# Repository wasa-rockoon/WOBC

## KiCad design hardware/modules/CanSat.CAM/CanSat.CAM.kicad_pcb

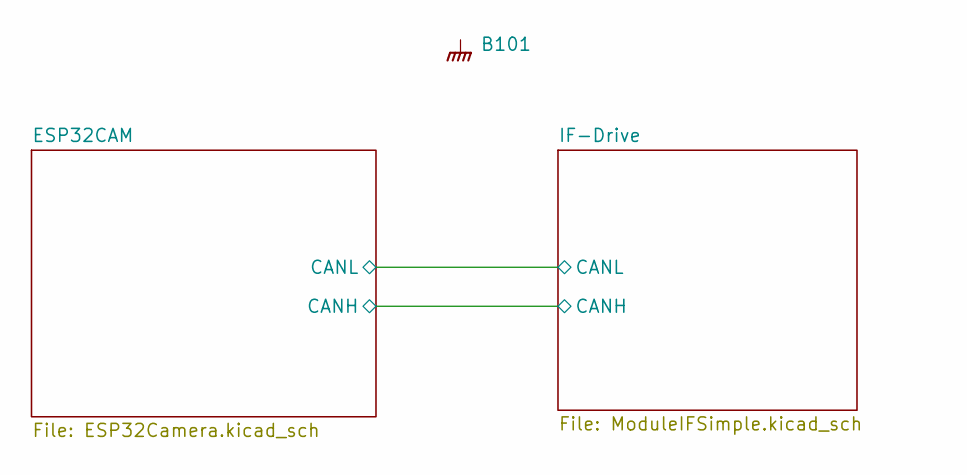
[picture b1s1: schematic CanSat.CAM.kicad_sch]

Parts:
B101: Board_0.5U_60x40

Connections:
GND: B101.GND; also elsewhere on the board

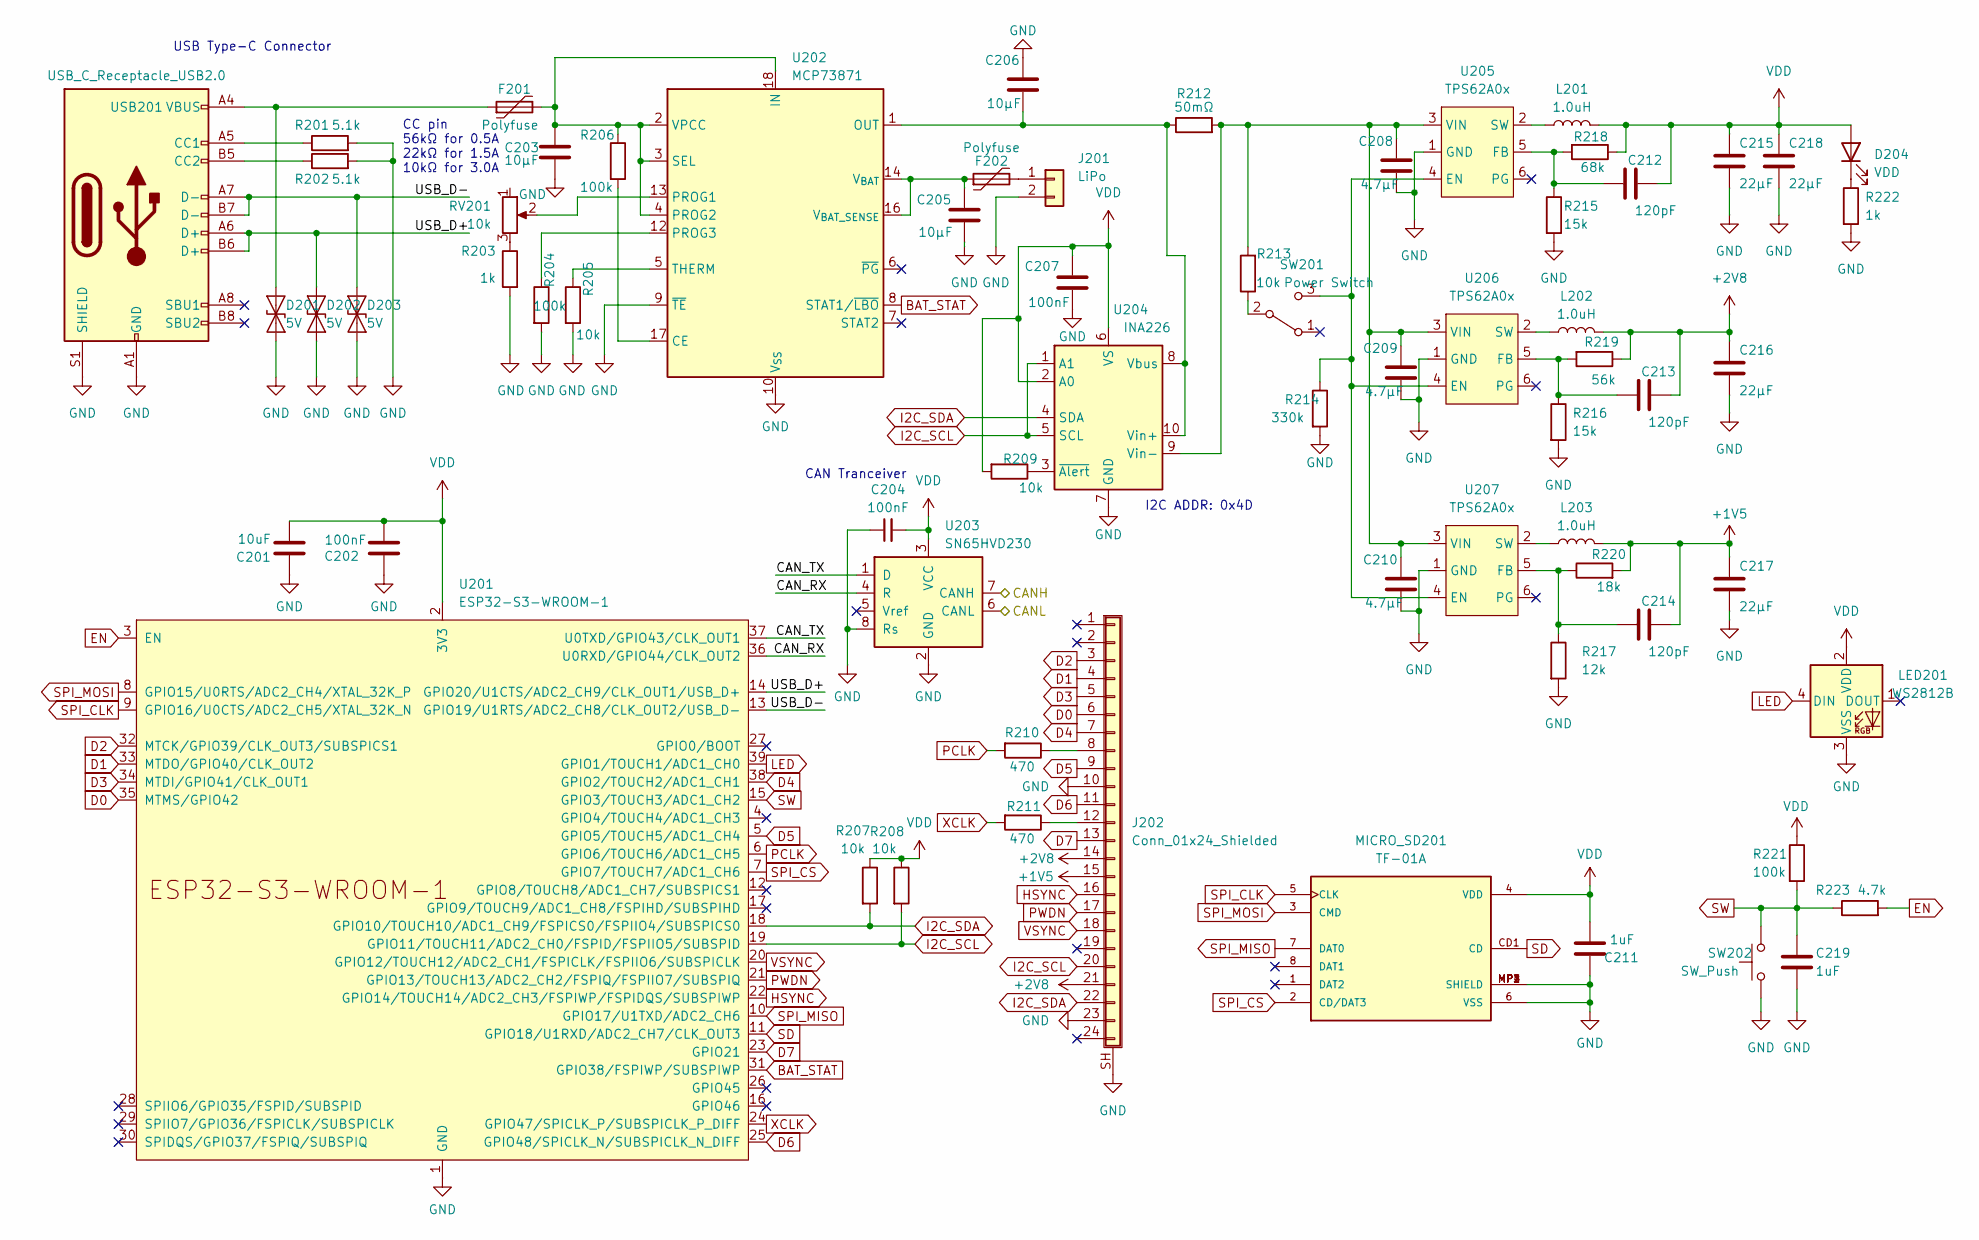
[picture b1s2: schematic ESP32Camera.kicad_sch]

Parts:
C201: 10uF; C_0603_1608Metric; LCSC C96446
C202, C204, C207: 100nF; C_0402_1005Metric; LCSC C1525
C203, C205, C206: 10µF; C_0603_1608Metric; LCSC C96446
C208, C209, C210: 4.7µF; C_0603_1608Metric; LCSC C19666
C211, C219: 1uF; C_0402_1005Metric; LCSC C52923
C212, C213, C214: 120pF; C_0402_1005Metric_Pad0.74x0.62mm_HandSolder; LCSC C307442
C215, C216, C217, C218: 22µF; C_0805_2012Metric; LCSC C45783
D201, D202, D203: 5V; D_SOD-882; LCSC C7420372
D204: VDD; LED_0805_2012Metric; LCSC C2297
F201, F202: Polyfuse; Fuse_1206_3216Metric; LCSC C883133
J201: LiPo; JST_PH_S2B-PH-K_1x02_P2.00mm_Horizontal
J202: Conn_01x24_Shielded; FPC-SMD_24P-P0.50_HCTL_HC-FPC-05-10-24RLTAG
L201, L202, L203: 1.0uH; L_Murata_DFE201610P; LCSC C882953
LED201: WS2812B; LED_XL-1615RGBC-WS2812B; LCSC C5349954
MICRO_SD201: TF-01A; LCSC C5155563
R201, R202: 5.1k; R_0402_1005Metric; LCSC C25905
R203, R222: 1k; R_0402_1005Metric; LCSC C11702
R204, R206, R221: 100k; R_0402_1005Metric; LCSC C25741
R205, R207, R208, R209, R213: 10k; R_0402_1005Metric; LCSC C25744
R210, R211: 470; R_0402_1005Metric; LCSC C25117
R212: 50mΩ; R_0805_2012Metric; LCSC C247602
R214: 330k; R_0402_1005Metric; LCSC C25778
R215, R216: 15k; R_0402_1005Metric; LCSC C25756
R217: 12k; R_0402_1005Metric; LCSC C25752
R218: 68k; R_0402_1005Metric; LCSC C36871
R219: 56k; R_0402_1005Metric; LCSC C25796
R220: 18k; R_0402_1005Metric; LCSC C25762
R223: 4.7k; R_0402_1005Metric; LCSC C25900
RV201: 10k; Potentiometer_Bourns_TC33X_Vertical; LCSC C719176
SW201: Power Switch; SW_Slide_SPDT_Straight_CK_OS102011MS2Q
SW202: SW_Push; TVAF06-A020B-R
U201: ESP32-S3-WROOM-1
U202: MCP73871; QFN-20-1EP_4x4mm_P0.5mm_EP2.5x2.5mm; LCSC C511310
U203: SN65HVD230; SOIC-8_3.9x4.9mm_P1.27mm; LCSC C12084
U204: INA226; VSSOP-10_3x3mm_P0.5mm; LCSC C49851
U205, U206, U207: TPS62A0x; SOT-563; LCSC C5350187
USB201: USB_C_Receptacle_USB2.0; USB_C_TYPEC-301S-ACP16X7; LCSC C2856766

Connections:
+1V5: C214.1, C217.1, J202.15, L203.2, R220.2
+2V8: C213.1, C216.1, J202.14, J202.21, L202.2, R219.1
/ESP32CAM/CANH: U203.7 (CANH); also elsewhere on the board
/ESP32CAM/CANL: U203.6 (CANL); also elsewhere on the board
/ESP32CAM/CAN_RX: U201.36 (U0RXD/GPIO44/CLK_OUT2), U203.4 (R)
/ESP32CAM/CAN_TX: U201.37 (U0TXD/GPIO43/CLK_OUT1), U203.1 (D)
/ESP32CAM/USB_D+: D202.2 (A2), U201.14 (GPIO20/U1CTS/ADC2_CH9/CLK_OUT1/USB_D+), USB201.A6 (D+), USB201.B6 (D+)
/ESP32CAM/USB_D-: D203.2 (A2), U201.13 (GPIO19/U1RTS/ADC2_CH8/CLK_OUT2/USB_D-), USB201.A7 (D-), USB201.B7 (D-)
BAT_STAT: U201.31 (GPIO38/FSPIWP/SUBSPIWP), U202.8 (STAT1/~LBO)
D0: J202.6, U201.35 (MTMS/GPIO42)
D1: J202.4, U201.33 (MTDO/GPIO40/CLK_OUT2)
D2: J202.3, U201.32 (MTCK/GPIO39/CLK_OUT3/SUBSPICS1)
D3: J202.5, U201.34 (MTDI/GPIO41/CLK_OUT1)
D4: J202.7, U201.38 (GPIO2/TOUCH2/ADC1_CH1)
D5: J202.9, U201.5 (GPIO5/TOUCH5/ADC1_CH4)
D6: J202.11, U201.25 (GPIO48/SPICLK_N/SUBSPICLK_N_DIFF)
D7: J202.13, U201.23 (GPIO21)
EN: R223.2, U201.3 (EN)
GND: C201.1, C202.1, C203.2, C204.1, C205.2, C206.1, C207.2, C208.2, C209.2, C210.2, C211.1, C215.2, C216.2, C217.2, C218.2, C219.2, D201.1 (A1), D202.1 (A1), D203.1 (A1), J201.2, J202.10, J202.23, J202.SH (Shield), LED201.3 (VSS), MICRO_SD201.6 (VSS), MICRO_SD201.MP1 (SHIELD), MICRO_SD201.MP2 (SHIELD), MICRO_SD201.MP3 (SHIELD), MICRO_SD201.MP4 (SHIELD), R201.2, R202.2, R203.2, R204.2, R205.2, R214.2, R215.2, R216.2, R217.2, R222.2, SW202.1, U201.1 (GND), U201.40 (GND), U201.41 (GND), U202.9 (~TE), U202.10 (V_{SS}), U202.11 (V_{SS}), U202.21 (V_{SS}), U203.2 (GND), U203.8 (Rs), U204.7 (GND), U205.1 (GND), U206.1 (GND), U207.1 (GND), USB201.A1 (GND), USB201.A12 (GND), USB201.B1 (GND), USB201.B12 (GND), USB201.S1 (SHIELD); also elsewhere on the board
HSYNC: J202.16, U201.22 (GPIO14/TOUCH14/ADC2_CH3/FSPIWP/FSPIDQS/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)
I2C_SCL: J202.20, R208.2, U201.19 (GPIO11/TOUCH11/ADC2_CH0/FSPID/FSPIIO5/S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), U204.1 (A1), U204.5 (SCL)
I2C_SDA: J202.22, R207.2, U201.18 (GPIO10/TOUCH10/ADC1_CH9/FSPICS0/FSPIIO4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), U204.4 (SDA)
LED: LED201.4 (DIN), U201.39 (GPIO1/TOUCH1/ADC1_CH0)
unnamed: D201.2 (A2), F201.1, USB201.A4 (VBUS), USB201.A9 (VBUS), USB201.B4 (VBUS), USB201.B9 (VBUS)
unnamed: D204.1 (K), R222.1
unnamed: F202.2, J201.1
unnamed: J202.8, R210.1
unnamed: J202.12, R211.1
unnamed: R203.1, RV201.3
unnamed: R213.1, SW201.2 (B)
unnamed: R214.1, SW201.3 (C), U205.4 (EN), U206.4 (EN), U207.4 (EN)
unnamed: R206.2, U202.17 (CE)
unnamed: RV201.2, U202.13 (PROG1)
unnamed: C203.1, F201.2, R206.1, U202.2 (VPCC), U202.3 (SEL), U202.4 (PROG2), U202.18 (IN), U202.19 (IN)
unnamed: R204.1, U202.12 (PROG3)
unnamed: R205.1, U202.5 (THERM)
unnamed: C205.1, F202.1, U202.14 (V_{BAT}), U202.15 (V_{BAT}), U202.16 (V_{BAT_SENSE})
unnamed: C206.2, R212.1, U202.1 (OUT), U202.20 (OUT), U204.8 (Vbus), U204.10 (Vin+)
unnamed: C208.1, C209.1, C210.1, R212.2, R213.2, U204.9 (Vin-), U205.3 (VIN), U206.3 (VIN), U207.3 (VIN)
unnamed: R209.1, U204.3 (~Alert)
unnamed: C212.2, R215.1, R218.2, U205.5 (FB)
unnamed: L201.1, U205.2 (SW)
unnamed: C213.2, R216.1, R219.2, U206.5 (FB)
unnamed: L202.1, U206.2 (SW)
unnamed: C214.2, R217.1, R220.1, U207.5 (FB)
unnamed: L203.1, U207.2 (SW)
unnamed: R201.1, USB201.A5 (CC1)
unnamed: R202.1, USB201.B5 (CC2)
PCLK: R210.2, U201.6 (GPIO6/TOUCH6/ADC1_CH5)
PWDN: J202.17, U201.21 (GPIO13/TOUCH13/ADC2_CH2/FSPIQ/FSPIIO7/S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)
SD: MICRO_SD201.CD1 (CD), U201.11 (GPIO18/U1RXD/ADC2_CH7/CLK_OUT3)
SPI_CLK: MICRO_SD201.5 (CLK), U201.9 (GPIO16/U0CTS/ADC2_CH5/XTAL_32K_N)
SPI_CS: MICRO_SD201.2 (CD/DAT3), U201.7 (GPIO7/TOUCH7/ADC1_CH6)
SPI_MISO: MICRO_SD201.7 (DAT0), U201.10 (GPIO17/U1TXD/ADC2_CH6)
SPI_MOSI: MICRO_SD201.3 (CMD), U201.8 (GPIO15/U0RTS/ADC2_CH4/XTAL_32K_P)
SW: C219.1, R221.2, R223.1, SW202.2, U201.15 (GPIO3/TOUCH3/ADC1_CH2)
VDD: C201.2, C202.2, C204.2, C207.1, C211.2, C212.1, C215.1, C218.1, D204.2 (A), L201.2, LED201.2 (VDD), MICRO_SD201.4 (VDD), R207.1, R208.1, R209.2, R218.1, R221.1, U201.2 (3V3), U203.3 (VCC), U204.2 (A0), U204.6 (VS)
VSYNC: J202.18, U201.20 (GPIO12/TOUCH12/ADC2_CH1/FSPICLK/FSPIIO6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)
XCLK: R211.2, U201.24 (GPIO47/SPICLK_P/SUBSPICLK_P_DIFF)

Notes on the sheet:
USB Type-C Connector
CAN Tranceiver
CC pin 56kΩ for 0.5A 22kΩ for 1.5A 10kΩ for 3.0A
I2C ADDR: 0x4D

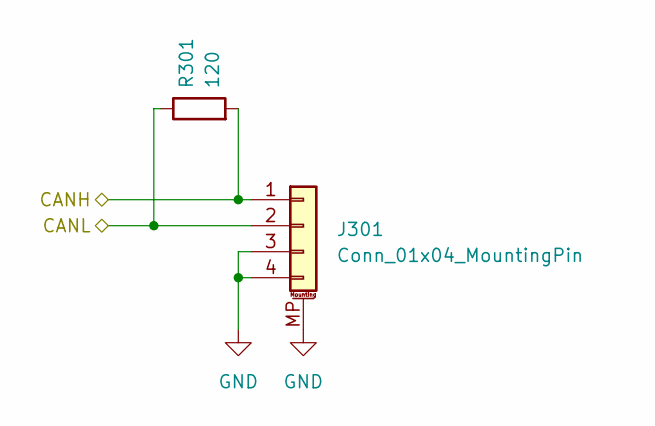
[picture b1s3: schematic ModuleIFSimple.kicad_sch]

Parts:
J301: Conn_01x04_MountingPin; Grove_4P_L_SMD
R301: 120; R_0402_1005Metric; LCSC C25079

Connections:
/ESP32CAM/CANH: J301.1, R301.2; also elsewhere on the board
/ESP32CAM/CANL: J301.2, R301.1; also elsewhere on the board
GND: J301.3, J301.4, J301.MP (MountPin); also elsewhere on the board

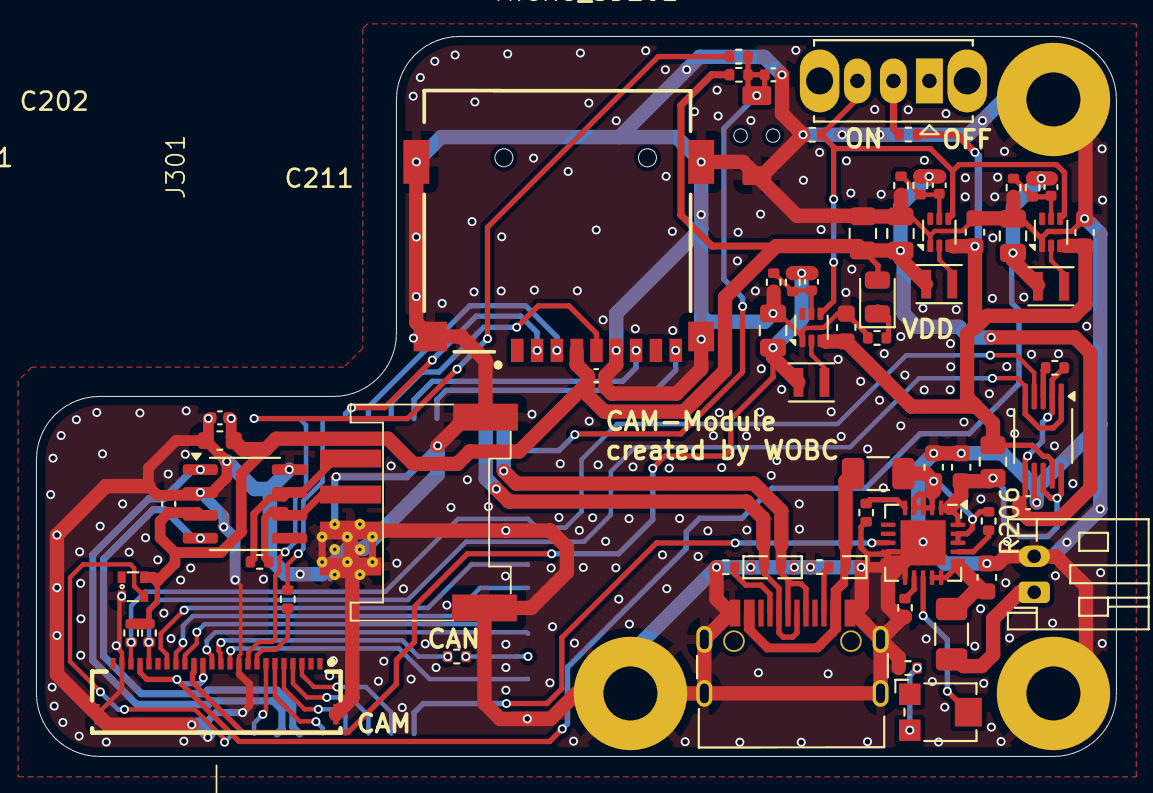
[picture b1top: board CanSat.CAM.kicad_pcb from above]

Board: 2 copper layers, 60.0 x 40.0 mm, 69 parts (1 on the bottom side), 59 nets.

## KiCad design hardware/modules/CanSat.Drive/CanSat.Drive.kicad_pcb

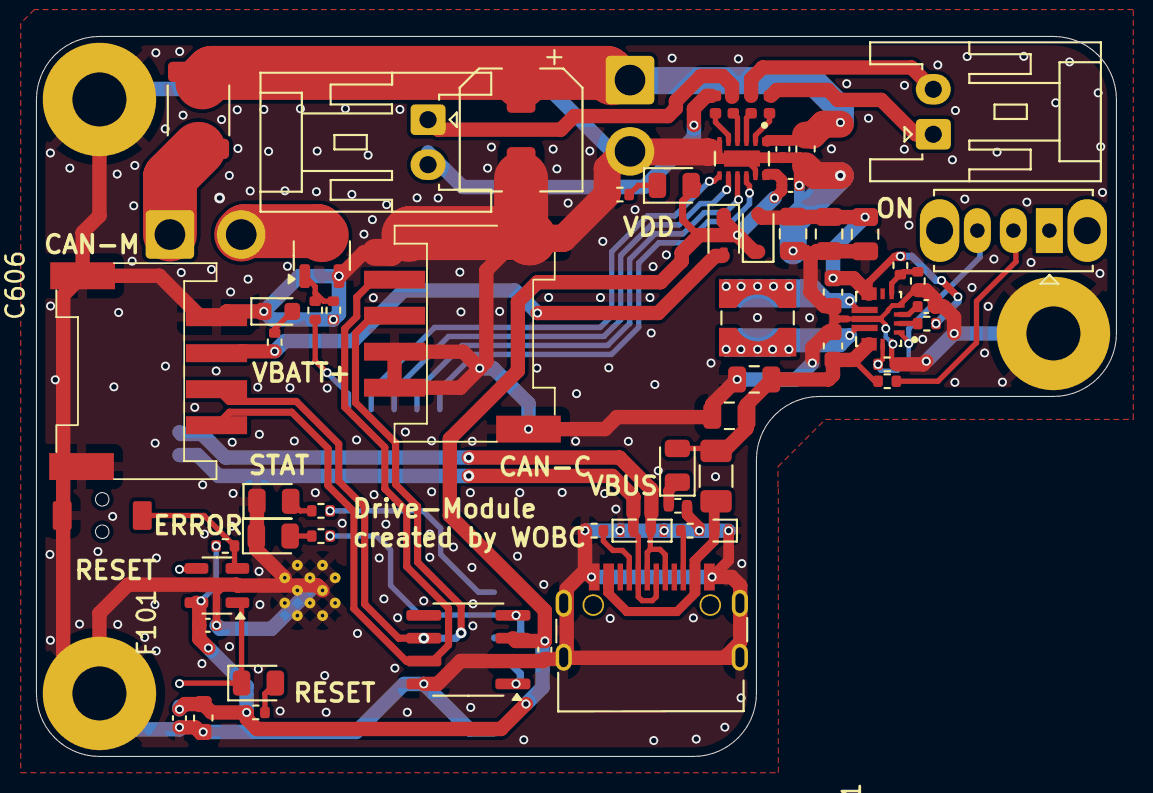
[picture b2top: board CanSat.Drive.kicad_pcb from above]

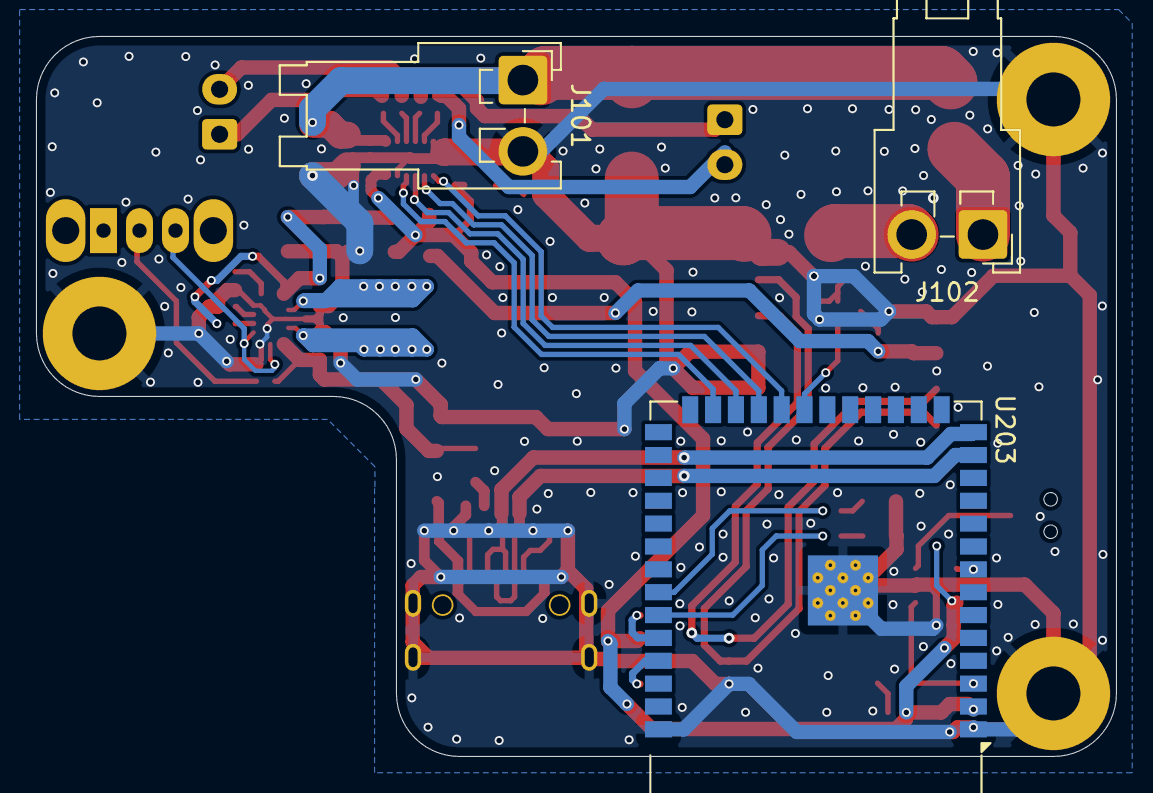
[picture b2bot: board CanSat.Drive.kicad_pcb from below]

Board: 2 copper layers, 60.0 x 40.0 mm, 66 parts (3 on the bottom side), 49 nets.

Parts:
B101: Board_0.5U_60x40
C201, C202, C204, C604: 100nF; C_0402_1005Metric
C203, C603, C605: 10uF; C_0603_1608Metric
C501: 100u; CP_Elec_6.3x7.7
C502: 10u; C_0603_1608Metric
C503, C504: 100n; C_0402_1005Metric
C601, C602, C606, C607, C608: 22uF; C_0805_2012Metric
D201, D202, D203: 5V; D_SOD-882
D204: RESET; LED_0805_2012Metric
D205: ERROR; LED_0805_2012Metric
D206: STAT; LED_0805_2012Metric
D601, D602: 1N5819WS; D_SOD-323
F101: Polyfuse; Fuse_1812_4532Metric
F601: Polyfuse; Fuse_1206_3216Metric
FB501, FB502, FB503, FB504: FerriteBead; L_0402_1005Metric
J101, J102: Conn_01x02_Pin; JST_VH_S2P-VH_1x02_P3.96mm_Horizontal
J301, J401: Conn_01x04_MountingPin; Grove_4P_L_SMD
J501, J502: Conn_01x02_Pin; JST_XA_S02B-XASK-1N-BN_1x02_P2.50mm_Horizontal
L601: L; L_Wuerth_WE-TPC-3816
LED301: Power; LED_0603_1608Metric
LED601: USB Power; LED_0805_2012Metric
LED602: VDD; LED_0805_2012Metric
Q101: Q_NMOS_DGS; SOT-23-3
R101, R201, R602: 10k; R_0402_1005Metric
R102: 10; R_0402_1005Metric
R202, R203: 5.1k; R_0402_1005Metric
R204, R205, R207: 470; R_0402_1005Metric
R301, R601, R607: 1k; R_0402_1005Metric
R603: 330k; R_0402_1005Metric
R604: 100k; R_0402_1005Metric
R605: 15k; R_0402_1005Metric
R606: 47k; R_0402_1005Metric
SW201: RESET_sw; TVAF06-A020B-R
SW601: Power Switch; SW_Slide_SPDT_Straight_CK_OS102011MS2Q
U201: TPS3820; SOT-23-5
U202: SN65HVD230; SOIC-8_3.9x4.9mm_P1.27mm
U203: ESP32-S3-WROOM-1
U501: SON50P300X200X80-13N
U601: TPS63070RNMR; VREG_TPS63070RNMR
USB201: USB_C_Receptacle_USB2.0; USB_C_TYPEC-301S-ACP16X7

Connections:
/AIN1: U203.25 (GPIO48/SPICLK_N/SUBSPICLK_N_DIFF), U501.10 (AIN1/APHASE)
/AIN2: U203.24 (GPIO47/SPICLK_P/SUBSPICLK_P_DIFF), U501.9 (AIN2/AENBL)
/BIN1: U203.23 (GPIO21), U501.8 (BIN1/BPHASE)
/BIN2: U203.22 (GPIO14/TOUCH14/ADC2_CH3/FSPIWP/FSPIDQS/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), U501.7 (BIN2/BENBL)
/CANH: J301.1, J401.1, U202.7 (CANH)
/CANL: J301.2, J401.2, U202.6 (CANL)
/ESP32Core/CAN_RX: U202.4 (R), U203.36 (U0RXD/GPIO44/CLK_OUT2)
/ESP32Core/CAN_TX: U202.1 (D), U203.37 (U0TXD/GPIO43/CLK_OUT1)
/ESP32Core/GPIO13: R102.1, U203.21 (GPIO13/TOUCH13/ADC2_CH2/FSPIQ/FSPIIO7/S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)
/ESP32Core/USB_D+: D202.2 (A2), U203.14 (GPIO20/U1CTS/ADC2_CH9/CLK_OUT1/USB_D+), USB201.A6 (D+), USB201.B6 (D+)
/ESP32Core/USB_D-: D203.2 (A2), U203.13 (GPIO19/U1RTS/ADC2_CH8/CLK_OUT2/USB_D-), USB201.A7 (D-), USB201.B7 (D-)
/ESP32Core/WDI: U201.4 (WDI), U203.8 (GPIO15/U0RTS/ADC2_CH4/XTAL_32K_P)
AOUT1: FB501.1, U501.2 (AOUT1)
AOUT2: FB502.1, U501.3 (AOUT2)
BOUT1: FB503.1, U501.4 (BOUT1)
BOUT2: FB504.1, U501.5 (BOUT2)
GND: B101.GND, C201.1, C202.1, C203.1, C204.2, C501.2, C502.2, C503.2, C504.2, C601.2, C602.2, C603.2, C604.2, C605.2, C606.2, C607.2, C608.2, D201.1 (A1), D202.1 (A1), D203.1 (A1), D205.1 (K), D206.1 (K), J101.2, J301.4, J301.MP (MountPin), J401.3, J401.4, J401.MP (MountPin), LED301.1 (K), Q101.2 (S), R101.2, R202.2, R203.2, R601.2, R603.2, R605.1, R607.2, SW201.2, U201.2 (GND), U202.2 (GND), U202.8 (Rs), U203.1 (GND), U203.40 (GND), U203.41 (GND), U501.6 (GND), U501.11 (MODE), U501.13 (GND), U601.4 (GND), U601.10 (PGND), U601.15 (VSEL), USB201.A1 (GND), USB201.A12 (GND), USB201.B1 (GND), USB201.B12 (GND), USB201.S1 (SHIELD)
unnamed: D204.2 (A), R204.2
unnamed: D205.2 (A), R205.2
unnamed: D206.2 (A), R207.2
unnamed: C605.1, C606.1, C607.1, C608.1, D601.2 (A2), R604.1, R606.2, U601.7_8 (VOUT)
unnamed: F101.2, J102.1
unnamed: J102.2, Q101.3 (D)
unnamed: FB501.2, J501.1
unnamed: FB502.2, J501.2
unnamed: FB503.2, J502.1
unnamed: FB504.2, J502.2
unnamed: LED301.2 (A), R301.1
unnamed: C601.1, C602.1, C603.1, F601.2, LED601.2 (A), R602.2, U601.12_13 (VIN)
unnamed: LED601.1 (K), R601.1
unnamed: LED602.1 (K), R607.1
unnamed: Q101.1 (G), R101.1, R102.2
unnamed: R602.1, SW601.2 (B)
unnamed: R603.1, SW601.3 (C), U601.1 (PS/SYNC), U601.14 (EN)
unnamed: R201.2, SW201.1, U201.3 (MR)
unnamed: R205.1, U203.34 (MTDI/GPIO41/CLK_OUT1)
unnamed: R207.1, U203.35 (MTMS/GPIO42)
unnamed: R605.2, R606.1, U601.5 (FB)
unnamed: L601.1, U601.11 (L1)
unnamed: L601.2, U601.9 (L2)
unnamed: R604.2, U601.2 (PG)
unnamed: C604.1, U601.3 (VAUX)
unnamed: R202.1, USB201.A5 (CC1)
unnamed: R203.1, USB201.B5 (CC2)
RESET: D204.1 (K), U201.1 (RESET), U203.3 (EN)
VBATT+: D602.2 (A2), J301.3, R301.2
VBUS: D201.2 (A2), F601.1, USB201.A4 (VBUS), USB201.A9 (VBUS), USB201.B4 (VBUS), USB201.B9 (VBUS)
VDD: C201.2, C202.2, C203.2, C204.1, C504.1, D601.1 (A1), D602.1 (A1), LED602.2 (A), R201.1, R204.1, U201.5 (VDD), U202.3 (VCC), U203.2 (3V3), U501.12 (VCC)
VM: C501.1, C502.1, C503.1, F101.1, J101.1, U501.1 (VM)

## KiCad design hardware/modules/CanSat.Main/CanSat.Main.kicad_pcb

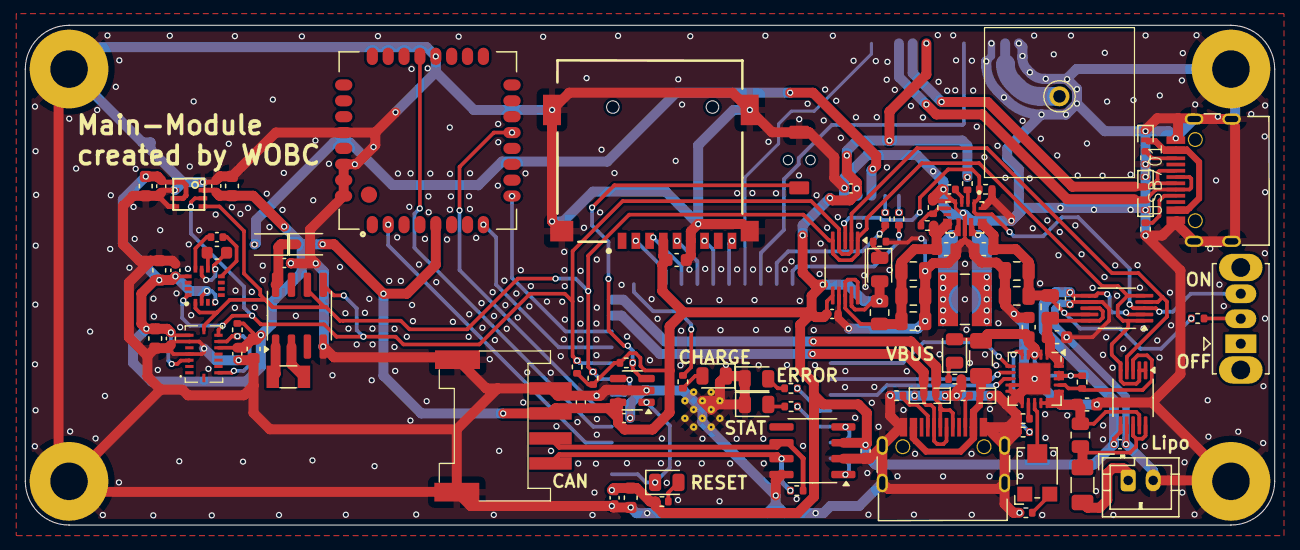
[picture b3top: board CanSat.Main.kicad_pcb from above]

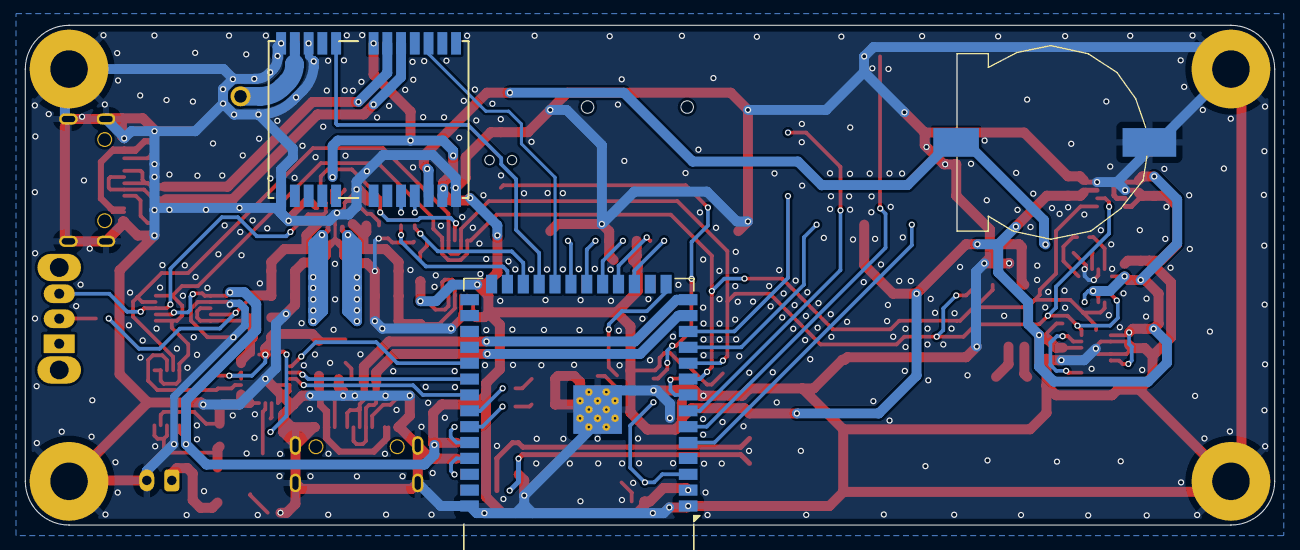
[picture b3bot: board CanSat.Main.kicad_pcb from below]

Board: 2 copper layers, 100.0 x 40.0 mm, 106 parts (3 on the bottom side), 76 nets.

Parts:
AE701: Antenna; GNSS_Antenna_1212
B101: Board_1U_100x40
BT101: Battery_Cell; cr1220
C201, C202, C204, C302, C307, C309, C314, C402, C501, C502, C507, C601, C701, C902, C903: 100nF; C_0402_1005Metric
C203, C301, C303, C304, C308, C310, C401: 10uF; C_0603_1608Metric
C305, C306, C311, C312, C313: 22uF; C_0805_2012Metric
C503, C504, C508, C901, C904: 10μF; C_0603_1608Metric
C505: 0.22μF; C_0402_1005Metric
C506: 4.7μF; C_0603_1608Metric
D201, D202, D203, D701: 5V; D_SOD-882
D204: RESET; LED_0805_2012Metric
D205: ERROR; LED_0805_2012Metric
D206: STAT; LED_0805_2012Metric
D401, D402: 1N5819WS; D_SOD-323
D702, D703: 5V; D_SOD-882D
F301, F302: Polyfuse; Fuse_1206_3216Metric
J301: LiPo; JST_PH_B2B-PH-K_1x02_P2.00mm_Vertical
J601: Conn_01x04_MountingPin; Grove_4P_L_SMD
L301: L; L_Wuerth_WE-TPC-3816
LED301: USB Power; LED_0805_2012Metric
LED302: CHARGE; LED_0805_2012Metric
LED303: VDD; LED_0805_2012Metric
MICRO_SD401: TF-01A
R201, R206, R208, R305, R308: 10k; R_0402_1005Metric
R202, R203, R701, R702: 5.1k; R_0402_1005Metric
R204, R205, R207: 470; R_0402_1005Metric
R301, R302, R303, R315: 1k; R_0402_1005Metric
R304, R306, R311: 100k; R_0402_1005Metric
R307, R310, R314: 50mΩ; R_0805_2012Metric
R309: 330k; R_0402_1005Metric
R312: 15k; R_0402_1005Metric
R313: 47k; R_0402_1005Metric
R501: 4.7K; R_0402_1005Metric
R601: 120; R_0402_1005Metric
R703, R704: 33; R_0402_1005Metric
RV301: 10k; Potentiometer_Bourns_TC33X_Vertical
SW201: RESET_sw; TVAF06-A020B-R
SW301: Power Switch; SW_Slide_SPDT_Straight_CK_OS102011MS2Q
U201: TPS3820; SOT-23-5
U202: SN65HVD230; SOIC-8_3.9x4.9mm_P1.27mm
U203: ESP32-S3-WROOM-1
U301: MCP73871-1CC; QFN-20-1EP_4x4mm_P0.5mm_EP2.5x2.5mm
U302, U303, U305: INA226; VSSOP-10_3x3mm_P0.5mm
U304: TPS63070RNMR; VREG_TPS63070RNMR
U401: PCF8563T; SOIC-8_3.9x4.9mm_P1.27mm
U501: BMI088
U502: QMC5883L; _HMC5883L
U701: NEO-M9N-00B; ATGM332D-5N31
U801: TWE-L-WX; TWELITE-SMD
U901: BME280
USB201, USB701: USB_C_Receptacle_USB2.0; USB_C_TYPEC-301S-ACP16X7
Y401: Crystal; Crystal_SMD_3215-2Pin_3.2x1.5mm

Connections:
+BATT: BT101.1 (+), D402.2 (A2), U701.22 (V_BCKP)
/CANH: J601.1, R601.2, U202.7 (CANH)
/CANL: J601.2, R601.1, U202.6 (CANL)
/ESP32Core/CAN_RX: U202.4 (R), U203.36 (U0RXD/GPIO44/CLK_OUT2)
/ESP32Core/CAN_TX: U202.1 (D), U203.37 (U0TXD/GPIO43/CLK_OUT1)
/ESP32Core/GPIO3/ADC1_CH2: R302.2, U203.15 (GPIO3/TOUCH3/ADC1_CH2)
/ESP32Core/USB_D+: D202.2 (A2), U203.14 (GPIO20/U1CTS/ADC2_CH9/CLK_OUT1/USB_D+), USB201.A6 (D+), USB201.B6 (D+)
/ESP32Core/USB_D-: D203.2 (A2), U203.13 (GPIO19/U1RTS/ADC2_CH8/CLK_OUT2/USB_D-), USB201.A7 (D-), USB201.B7 (D-)
/ESP32Core/WDI: U201.4 (WDI), U203.8 (GPIO15/U0RTS/ADC2_CH4/XTAL_32K_P)
/GPS/USB_D+: D702.2 (A2), U701.6 (USB_DP), USB701.A6 (D+), USB701.B6 (D+)
/GPS/USB_D-: D703.2 (A2), U701.5 (USB_DM), USB701.A7 (D-), USB701.B7 (D-)
/I2C_SCL: R206.2, U203.9 (GPIO16/U0CTS/ADC2_CH5/XTAL_32K_N), U302.1 (A1), U302.5 (SCL), U303.1 (A1), U303.2 (A0), U303.5 (SCL), U305.1 (A1), U305.5 (SCL), U401.6 (SCL), U501.8 (SCL/SCK), U502.1 (SCL), U901.4 (SCK)
/I2C_SDA: R208.2, U203.10 (GPIO17/U1TXD/ADC2_CH6), U302.4 (SDA), U303.4 (SDA), U305.2 (A0), U305.4 (SDA), U401.5 (SDA), U501.9 (SDA/SDI), U502.16 (SDA), U901.3 (SDI)
/PG: U203.31 (GPIO38/FSPIWP/SUBSPIWP), U301.6 (~PG)
/PRG: U203.5 (GPIO5/TOUCH5/ADC1_CH4), U801.2 (DO1/PWM3)
/Power/PROG: RV301.2, U301.13 (PROG1)
/RESET: U203.23 (GPIO21), U701.8 (RESET_N)
/RST: U203.6 (GPIO6/TOUCH6/ADC1_CH5), U801.21 (~RESET)
/RX: R703.1, U203.24 (GPIO47/SPICLK_P/SUBSPICLK_P_DIFF)
/RXD: U203.12 (GPIO8/TOUCH8/ADC1_CH7/SUBSPICS1), U801.9 (DIO7/RX)
/SD_CLK: MICRO_SD401.5 (CLK), U203.19 (GPIO11/TOUCH11/ADC2_CH0/FSPID/FSPIIO5/S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)
/SD_DET: MICRO_SD401.CD1 (CD), U203.21 (GPIO13/TOUCH13/ADC2_CH2/FSPIQ/FSPIIO7/S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)
/SD_MISO: MICRO_SD401.7 (DAT0), U203.20 (GPIO12/TOUCH12/ADC2_CH1/FSPICLK/FSPIIO6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)
/SD_MOSI: MICRO_SD401.3 (CMD), U203.18 (GPIO10/TOUCH10/ADC1_CH9/FSPICS0/FSPIIO4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)
/SD_SS: MICRO_SD401.2 (CD/DAT3), U203.17 (GPIO9/TOUCH9/ADC1_CH8/FSPIHD/SUBSPIHD)
/SET: U203.7 (GPIO7/TOUCH7/ADC1_CH6), U801.13 (DIO12/DI1)
/STAT1: U203.33 (MTDO/GPIO40/CLK_OUT2), U301.8 (STAT1/~LBO)
/STAT2: U203.32 (MTCK/GPIO39/CLK_OUT3/SUBSPICS1), U301.7 (STAT2)
/TIMEPULSE: U203.22 (GPIO14/TOUCH14/ADC2_CH3/FSPIWP/FSPIDQS/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), U701.3 (TIMEPULSE)
/TX: R704.1, U203.25 (GPIO48/SPICLK_N/SUBSPICLK_N_DIFF)
/TXD: U203.11 (GPIO18/U1RXD/ADC2_CH7/CLK_OUT3), U801.8 (DIO6/TX)
GND: B101.GND, BT101.2 (-), C201.1, C202.1, C203.1, C204.2, C301.2, C302.2, C303.2, C304.2, C305.2, C306.2, C307.2, C308.2, C309.2, C310.2, C311.2, C312.2, C313.2, C314.2, C401.2, C402.1, C501.2, C502.2, C503.2, C504.2, C506.2, C507.2, C508.2, C601.1, C701.1, C901.2, C902.2, C903.2, C904.2, D201.1 (A1), D202.1 (A1), D203.1 (A1), D205.1 (K), D206.1 (K), D701.1 (A1), D702.1 (A1), D703.1 (A1), J301.2, J601.4, J601.MP (MountPin), LED302.1 (K), MICRO_SD401.6 (VSS), MICRO_SD401.MP1 (SHIELD), MICRO_SD401.MP2 (SHIELD), MICRO_SD401.MP3 (SHIELD), MICRO_SD401.MP4 (SHIELD), R202.2, R203.2, R301.2, R303.2, R304.2, R305.1, R309.2, R312.1, R315.2, R701.2, R702.2, SW201.2, U201.2 (GND), U202.2 (GND), U202.8 (Rs), U203.1 (GND), U203.40 (GND), U203.41 (GND), U301.9 (~TE), U301.10 (V_{SS}), U301.11 (V_{SS}), U301.21 (V_{SS}), U302.7 (GND), U303.7 (GND), U304.4 (GND), U304.10 (PGND), U304.15 (VSEL), U305.7 (GND), U401.4 (VSS), U501.4 (GNDA), U501.6 (GNDIO), U502.9 (GND), U502.11 (GND), U701.10 (GND), U701.12 (GND), U701.13 (GND), U701.24 (GND), U801.20 (GND), U801.28 (GND), U801.30 (GND), U801.31 (GND), U801.32 (GND), U901.1 (GND), U901.5 (SDO), U901.7 (GND), USB201.A1 (GND), USB201.A12 (GND), USB201.B1 (GND), USB201.B12 (GND), USB201.S1 (SHIELD), USB701.A1 (GND), USB701.A12 (GND), USB701.B1 (GND), USB701.B12 (GND), USB701.S1 (SHIELD)
GPSANT1: AE701.1 (A), U701.11 (RF_IN)
unnamed: D204.2 (A), R204.2
unnamed: D205.2 (A), R205.2
unnamed: D206.2 (A), R207.2
unnamed: C402.2, D401.1 (A1), D402.1 (A1), U401.8 (VDD)
unnamed: D701.2 (A2), USB701.A4 (VBUS), USB701.A9 (VBUS), USB701.B4 (VBUS), USB701.B9 (VBUS)
unnamed: F302.2, J301.1
unnamed: C301.1, F301.2, LED301.2 (A), R306.1, U301.2 (VPCC), U301.3 (SEL), U301.4 (PROG2), U301.18 (IN), U301.19 (IN)
unnamed: LED301.1 (K), R301.1
unnamed: LED302.2 (A), R302.1
unnamed: LED303.1 (K), R315.1
unnamed: R303.1, RV301.3
unnamed: R308.1, SW301.2 (B)
unnamed: R309.1, SW301.3 (C), U302.3 (~Alert), U304.1 (PS/SYNC), U304.14 (EN), U305.3 (~Alert)
unnamed: R201.2, SW201.1, U201.3 (MR)
unnamed: R205.1, U203.34 (MTDI/GPIO41/CLK_OUT1)
unnamed: R207.1, U203.35 (MTMS/GPIO42)
unnamed: R306.2, U301.17 (CE), U303.3 (~Alert)
unnamed: R304.1, U301.12 (PROG3)
unnamed: R305.2, U301.5 (THERM)
unnamed: C304.1, R310.1, U301.14 (V_{BAT}), U301.15 (V_{BAT}), U301.16 (V_{BAT_SENSE}), U303.9 (Vin-)
unnamed: C303.1, R307.1, U301.1 (OUT), U301.20 (OUT), U302.8 (Vbus), U302.10 (Vin+)
unnamed: C305.1, C306.1, C308.1, R307.2, R308.2, U302.9 (Vin-), U304.12_13 (VIN)
unnamed: F302.1, R310.2, U303.8 (Vbus), U303.10 (Vin+)
unnamed: R312.2, R313.1, U304.5 (FB)
unnamed: L301.1, U304.11 (L1)
unnamed: L301.2, U304.9 (L2)
unnamed: R311.2, U304.2 (PG)
unnamed: C309.1, U304.3 (VAUX)
unnamed: U401.1 (OSCI), Y401.1
unnamed: U401.2 (OSCO), Y401.2
unnamed: R501.1, U501.10 (SDO2), U501.15 (SDO1)
unnamed: C506.1, U502.10 (C1)
unnamed: C505.1, U502.12 (SETC)
unnamed: C505.2, U502.8 (STEP)
unnamed: R703.2, U701.21 (RXD_/_SPI_MOSI)
unnamed: R704.2, U701.20 (TXD_/_SPI_MISO)
unnamed: R202.1, USB201.A5 (CC1)
unnamed: R203.1, USB201.B5 (CC2)
unnamed: R701.1, USB701.A5 (CC1)
unnamed: R702.1, USB701.B5 (CC2)
RESET: D204.1 (K), U201.1 (RESET), U203.3 (EN)
VBUS: D201.2 (A2), F301.1, USB201.A4 (VBUS), USB201.A9 (VBUS), USB201.B4 (VBUS), USB201.B9 (VBUS)
VDD: C201.2, C202.2, C203.2, C204.1, C302.1, C307.1, C310.1, C311.1, C312.1, C313.1, C314.1, C401.1, C501.1, C502.1, C503.1, C504.1, C507.1, C508.1, C601.2, C701.2, C901.1, C902.1, C903.1, C904.1, D401.2 (A2), J601.3, LED303.2 (A), MICRO_SD401.4 (VDD), R201.1, R204.1, R206.1, R208.1, R311.1, R313.2, R314.1, R314.2, R501.2, U201.5 (VDD), U202.3 (VCC), U203.2 (3V3), U302.2 (A0), U302.6 (VS), U303.6 (VS), U304.7_8 (VOUT), U305.6 (VS), U305.8 (Vbus), U305.9 (Vin-), U305.10 (Vin+), U501.3 (VDD), U501.7 (PS), U501.11 (VDDIO), U502.2 (VDD), U502.4 (S1), U502.13 (VDDIO), U701.7 (V_USB), U701.23 (VCC), U801.5 (VCC), U901.2 (CSB), U901.6 (VDDIO), U901.8 (VDD)

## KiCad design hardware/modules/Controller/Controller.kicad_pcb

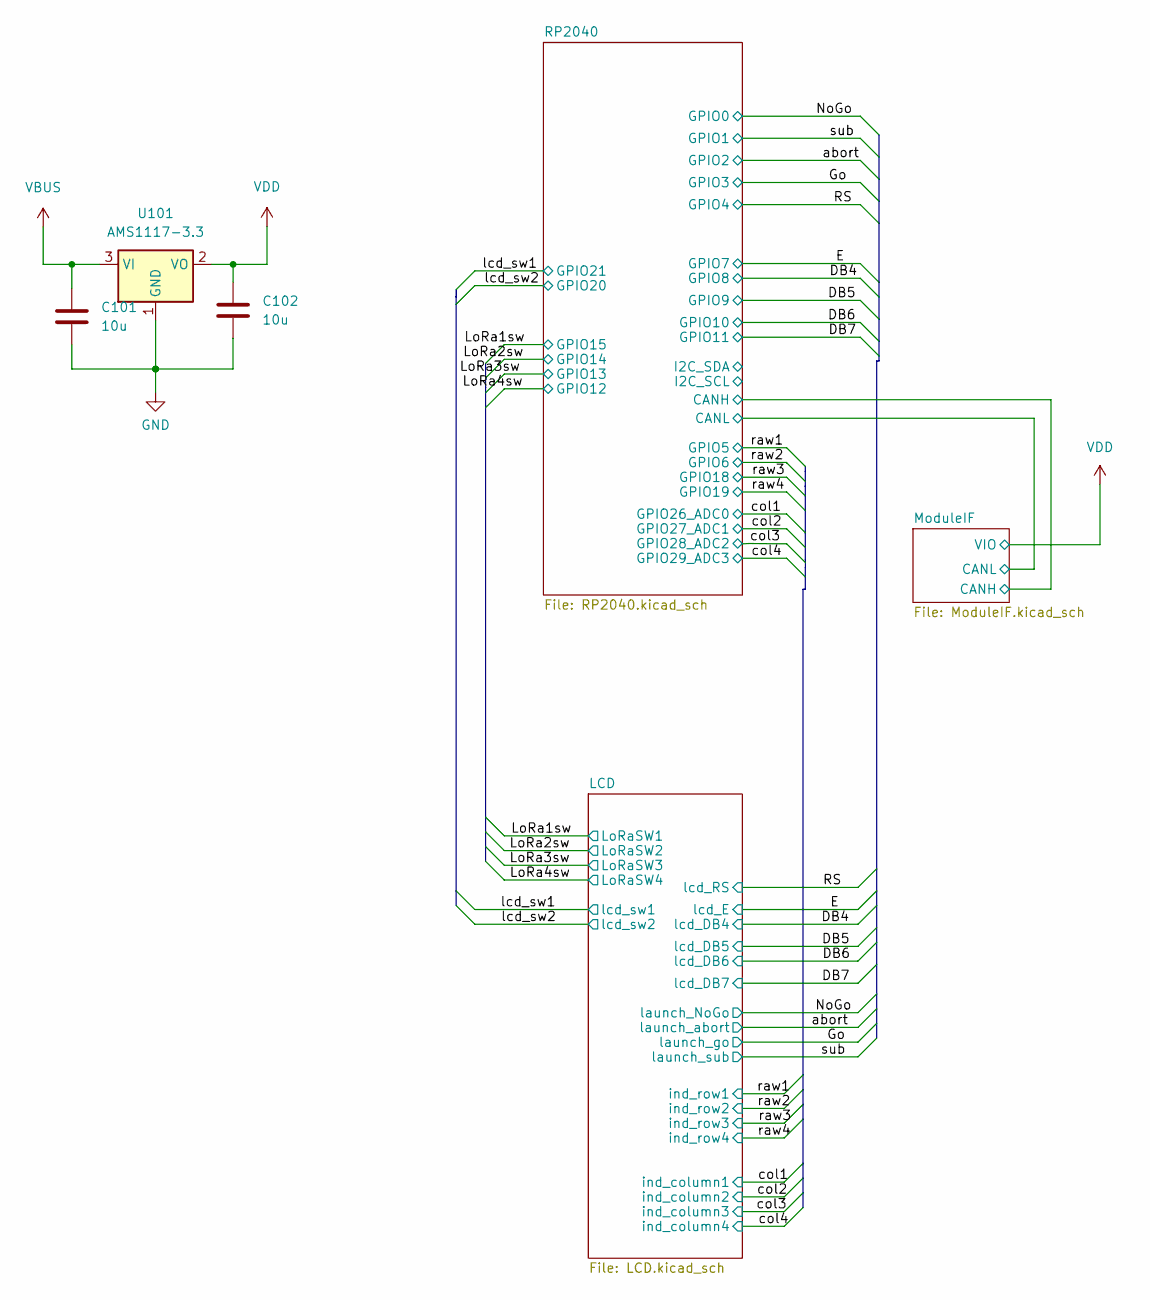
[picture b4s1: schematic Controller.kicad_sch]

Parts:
C101, C102: 10u; C_0603_1608Metric; LCSC C96446
U101: AMS1117-3.3; SOT-223-3_TabPin2; LCSC C6186

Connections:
GND: C101.2, C102.2, U101.1 (GND); also elsewhere on the board
VBUS: C101.1, U101.3 (VI); also elsewhere on the board
VDD: C102.1, U101.2 (VO); also elsewhere on the board
